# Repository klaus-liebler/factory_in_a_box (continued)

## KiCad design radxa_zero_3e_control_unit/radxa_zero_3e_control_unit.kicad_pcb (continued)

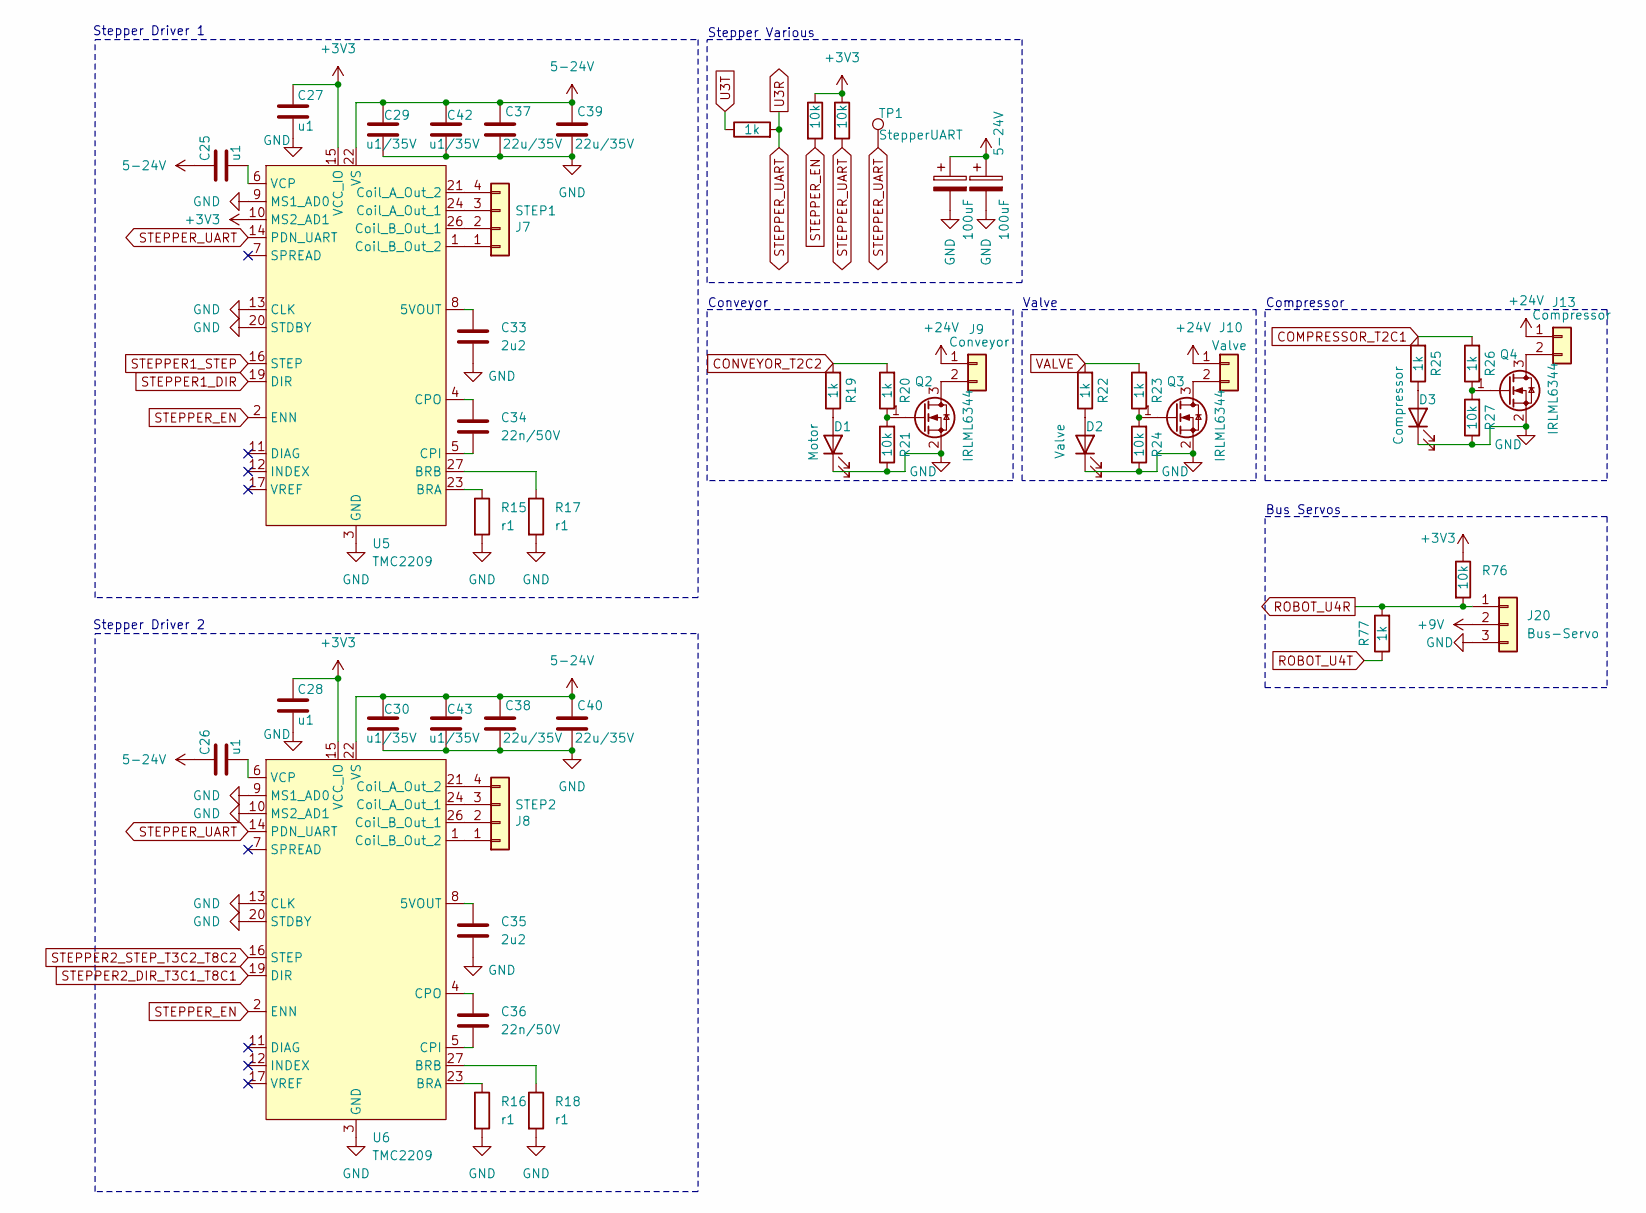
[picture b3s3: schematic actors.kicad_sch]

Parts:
C23, C24: 100uF; CP_Radial_D8.0mm_P2.50mm
C25, C26: u1; C_0805_2012Metric; MPN GRM033R61A104KE15D
C27, C28: u1; C_0402_1005Metric; MPN GRM033R61A104KE15D
C29, C30, C42, C43: u1/35V; C_0805_2012Metric; MPN CC0603KRX7R9BB104
C33, C35: 2u2; C_0402_1005Metric; MPN CL05A225MQ5NSNC
C34, C36: 22n/50V; C_0402_1005Metric; MPN GRM155R71H223KA12D
C37, C38, C39, C40: 22u/35V; C_0805_2012Metric; MPN CGA0805X5R226M350MT
D1: Motor; LED_1206_3216Metric_ReverseMount; MPN LTST-C230KRKT
D2: Valve; LED_1206_3216Metric_ReverseMount; MPN LTST-C230KRKT
D3: Compressor; LED_1206_3216Metric_ReverseMount; MPN LTST-C230KRKT
J7: STEP1; JST_XH_B4B-XH-A_1x04_P2.50mm_Vertical_smaller; MPN XH-4AW
J8: STEP2; JST_XH_B4B-XH-A_1x04_P2.50mm_Vertical_smaller; MPN XH-4AW
J9: Conveyor; PhoenixContact_MC_1,5_2-G-3.5_1x02_P3.50mm_Horizontal_small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
J10: Valve; PhoenixContact_MC_1,5_2-G-3.5_1x02_P3.50mm_Horizontal_small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
J13: Compressor; PhoenixContact_MC_1,5_2-G-3.5_1x02_P3.50mm_Horizontal_small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
J20: Bus-Servo; Molex_SPOX_5267-03A_1x03_P2.50mm_Vertical; MPN 5267-03A / 22035035
Q2, Q3, Q4: IRLML6344; SOT-23; MPN AO3400
R1, R77: 1k; R_0402_1005Metric
R9, R10, R76: 10k; R_0402_1005Metric
R15, R16, R17, R18: r1; R_1206_3216Metric; MPN FRM121WFR100TM
R19, R20, R22, R23, R25, R26: 1k; R_0402_1005Metric; MPN 0402WGF1001TCE
R21, R24, R27: 10k; R_0402_1005Metric; MPN 0201WMF1002TEE
TP1: StepperUART; TestPoint_THTPad_D1.0mm_Drill0.5mm
U5, U6: TMC2209; QFN-28-1EP_5x5mm_P0.5mm_EP3.75x3.75mm_ThermalVias; MPN TMC2209-LA-T

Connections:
5-24V: C23.1, C24.1, C25.1, C26.1, C29.1, C30.1, C37.2, C38.2, C39.2, C40.2, C42.1, C43.1, U5.22 (VS), U5.28 (VS), U6.22 (VS), U6.28 (VS); also elsewhere on the board
+3V3: C27.1, C28.1, R9.1, R10.1, R76.1, U5.10 (MS2_AD1), U5.15 (VCC_IO), U6.15 (VCC_IO); also elsewhere on the board
+9V: J20.2; also elsewhere on the board
+24V: J9.1, J10.1, J13.1; also elsewhere on the board
COMPRESSOR_T2C1: R25.2, R26.2; also elsewhere on the board
CONVEYOR_T2C2: R19.2, R20.2; also elsewhere on the board
GND: C23.2, C24.2, C27.2, C28.2, C29.2, C30.2, C33.2, C35.2, C37.1, C38.1, C39.1, C40.1, C42.2, C43.2, D1.1 (K), D2.1 (K), D3.1 (K), J20.3, Q2.2 (S), Q3.2 (S), Q4.2 (S), R15.2, R16.2, R17.2, R18.2, R21.1, R24.1, R27.1, U5.3 (GND), U5.9 (MS1_AD0), U5.13 (CLK), U5.18 (GND), U5.20 (STDBY), U5.25 (GND), U5.29 (PAD), U6.3 (GND), U6.9 (MS1_AD0), U6.10 (MS2_AD1), U6.13 (CLK), U6.18 (GND), U6.20 (STDBY), U6.25 (GND), U6.29 (PAD); also elsewhere on the board
unnamed: D1.2 (A), R19.1
unnamed: D2.2 (A), R22.1
unnamed: D3.2 (A), R25.1
unnamed: J7.1, U5.1 (Coil_B_Out_2)
unnamed: J7.2, U5.26 (Coil_B_Out_1)
unnamed: J7.3, U5.24 (Coil_A_Out_1)
unnamed: J7.4, U5.21 (Coil_A_Out_2)
unnamed: J8.1, U6.1 (Coil_B_Out_2)
unnamed: J8.2, U6.26 (Coil_B_Out_1)
unnamed: J8.3, U6.24 (Coil_A_Out_1)
unnamed: J8.4, U6.21 (Coil_A_Out_2)
unnamed: J9.2, Q2.3 (D)
unnamed: J10.2, Q3.3 (D)
unnamed: J13.2, Q4.3 (D)
unnamed: Q2.1 (G), R20.1, R21.2
unnamed: Q3.1 (G), R23.1, R24.2
unnamed: Q4.1 (G), R26.1, R27.2
unnamed: C33.1, U5.8 (5VOUT)
unnamed: R15.1, U5.23 (BRA)
unnamed: R17.1, U5.27 (BRB)
unnamed: C34.2, U5.5 (CPI)
unnamed: C34.1, U5.4 (CPO)
unnamed: C25.2, U5.6 (VCP)
unnamed: C35.1, U6.8 (5VOUT)
unnamed: R16.1, U6.23 (BRA)
unnamed: R18.1, U6.27 (BRB)
unnamed: C36.2, U6.5 (CPI)
unnamed: C36.1, U6.4 (CPO)
unnamed: C26.2, U6.6 (VCP)
ROBOT_U4R: J20.1, R76.2, R77.2; also elsewhere on the board
ROBOT_U4T: R77.1; also elsewhere on the board
STEPPER1_DIR: U5.19 (DIR); also elsewhere on the board
STEPPER1_STEP: U5.16 (STEP); also elsewhere on the board
STEPPER2_DIR_T3C1_T8C1: U6.19 (DIR); also elsewhere on the board
STEPPER2_STEP_T3C2_T8C2: U6.16 (STEP); also elsewhere on the board
STEPPER_EN: R9.2, U5.2 (ENN), U6.2 (ENN); also elsewhere on the board
STEPPER_UART: R1.2, R10.2, TP1.1, U5.14 (PDN_UART), U6.14 (PDN_UART); also elsewhere on the board
U3T: R1.1; also elsewhere on the board
VALVE: R22.2, R23.2; also elsewhere on the board

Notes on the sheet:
Stepper Driver 2
Valve
Stepper Various
Bus Servos
Stepper Driver 1
Conveyor
Compressor

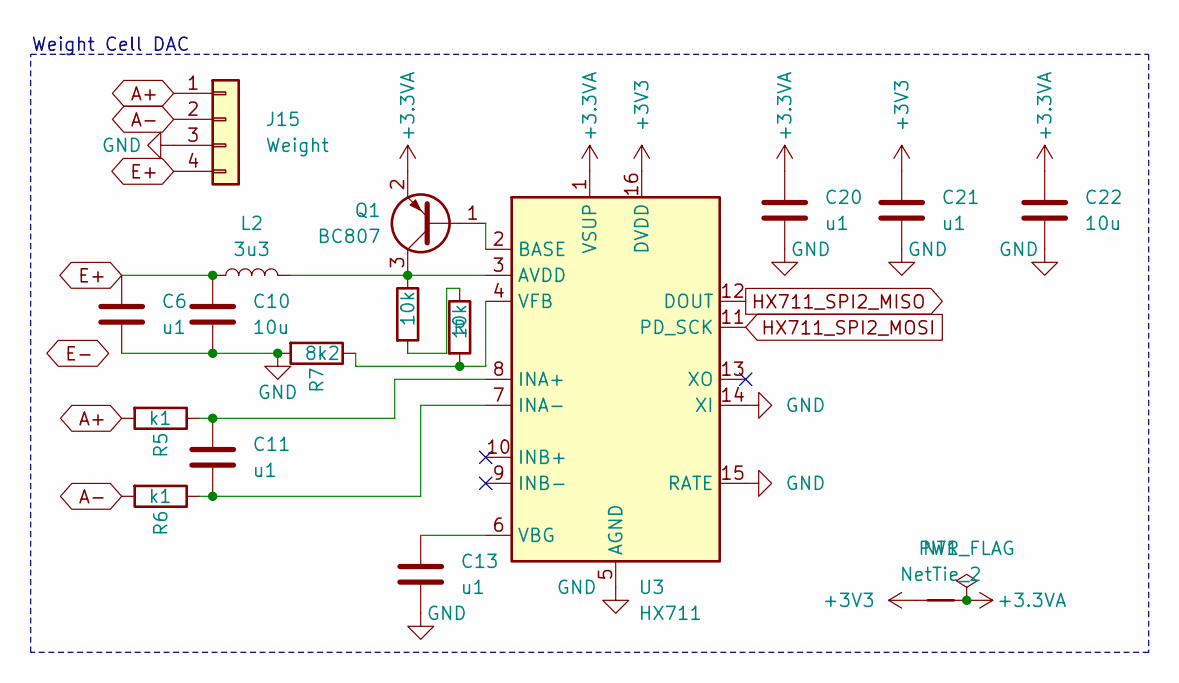
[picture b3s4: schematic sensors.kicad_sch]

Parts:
C6, C11, C13, C20, C21: u1; C_0402_1005Metric
C10, C22: 10u; C_0805_2012Metric_Pad1.18x1.45mm_HandSolder
J15: Weight; JST_XH_B4B-XH-A_1x04_P2.50mm_Vertical_smaller
L2: 3u3; L_0805_2012Metric_Pad1.15x1.40mm_HandSolder
NT1: NetTie_2; NetTie-2_SMD_Pad0.5mm
Q1: BC807; SOT-23_smaller
R5, R6: k1; R_0402_1005Metric
R7: 8k2; R_0402_1005Metric
R8, R11: 10k; R_0402_1005Metric
U3: HX711; SOIC-16_3.9x9.9mm_P1.27mm

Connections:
+3.3VA: C20.1, C22.1, NT1.2, Q1.2 (E), U3.1 (VSUP)
+3V3: C21.1, NT1.1, U3.16 (DVDD); also elsewhere on the board
A+: J15.1, R5.2
A-: J15.2, R6.2
E+: C6.1, C10.1, J15.4, L2.1
GND: C6.2, C10.2, C13.2, C20.2, C21.2, C22.2, J15.3, R7.2, U3.5 (AGND), U3.14 (XI), U3.15 (RATE); also elsewhere on the board
HX711_SPI2_MISO: U3.12 (DOUT); also elsewhere on the board
HX711_SPI2_MOSI: U3.11 (PD_SCK); also elsewhere on the board
unnamed: Q1.1 (B), U3.2 (BASE)
unnamed: L2.2, Q1.3 (C), R8.1, U3.3 (AVDD)
unnamed: R8.2, R11.1
unnamed: C11.1, R5.1, U3.8 (INA+)
unnamed: C11.2, R6.1, U3.7 (INA-)
unnamed: C13.1, U3.6 (VBG)
unnamed: R7.1, R11.2, U3.4 (VFB)

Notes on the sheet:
Weight Cell DAC

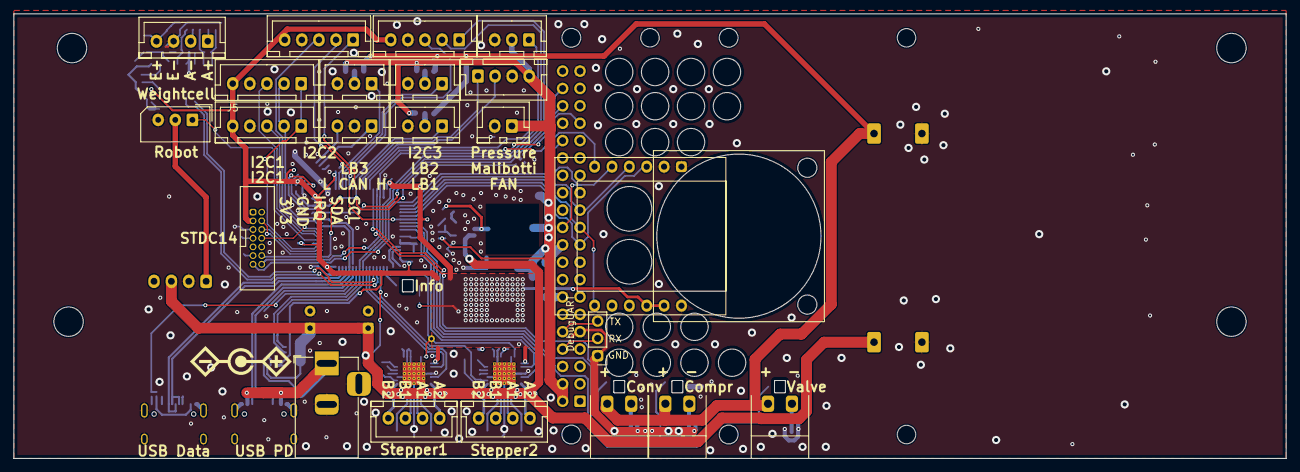
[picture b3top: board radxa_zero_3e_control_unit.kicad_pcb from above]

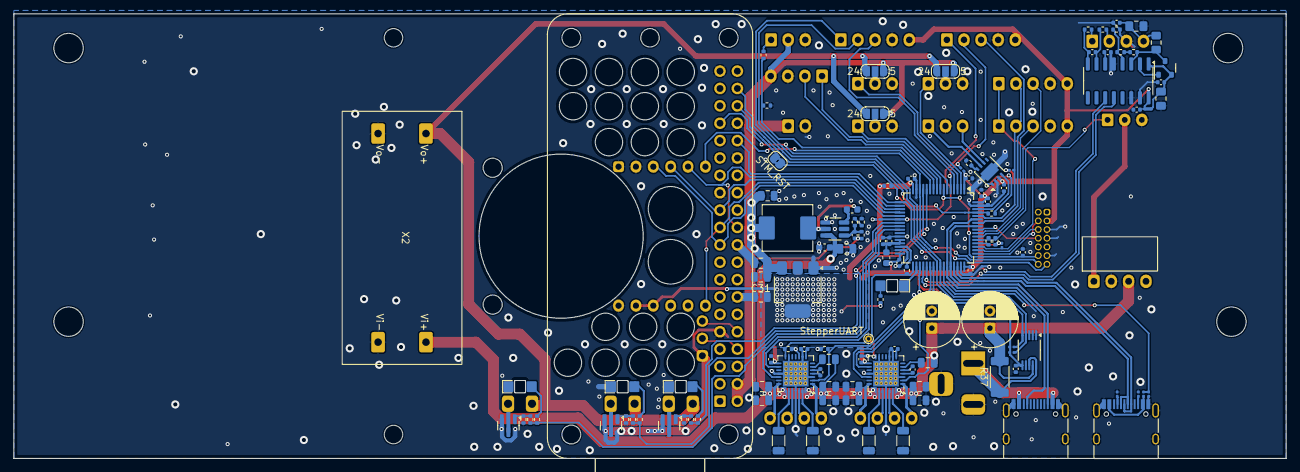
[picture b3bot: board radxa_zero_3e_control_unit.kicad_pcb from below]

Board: 2 copper layers, 186.0 x 65.0 mm, 148 parts (117 on the bottom side), 116 nets.

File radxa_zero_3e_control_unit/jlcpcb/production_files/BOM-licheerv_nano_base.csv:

Comment,Designator,Footprint,LCSC,Quantity
56p,C4,C_0402_1005Metric,C107007,1
1k,"R1,R19,R20,R22,R23,R25,R26",R_0402_1005Metric,C11702,7
Motor,"D1,D2,D3",LED_1206_3216Metric_ReverseMount,C125107,3
u1/35V,"C1,C3",C_0603_1608Metric,C14663,2
3u3,L2,L_0805_2012Metric_Pad1.15x1.40mm_HandSolder,C162585,1
USB STM32,"J1,J22",USB_C_Receptacle_HRO_TYPE-C-31-M-12_smaller,C165948,2
2u2,"C33,C35,C8",C_0402_1005Metric,C170151,3
TPS54202DDC,U1,SOT-23-6_Handsoldering,C191884,1
600R,FB1,L_0603_1608Metric,C19330,1
TMC2209,"U5,U6",QFN-28-1EP_5x5mm_P0.5mm_EP3.75x3.75mm_ThermalVias,C2150710,2
4u7,C14,C_0402_1005Metric,C23733,1
k1,"R5,R6",R_0402_1005Metric,C25076,2
r1,"R15,R16,R17,R18",R_1206_3216Metric,C25334,4
3k3,R4,R_0402_1005Metric,C25890,1
8k2,R7,R_0402_1005Metric,C25924,1
5k1,"R13,R28",R_0201_0603Metric,C270344,2
22n/50V,"C34,C36",C_0402_1005Metric,C337699,2
IRLML6344,"Q2,Q3,Q4",SOT-23,C347475,3
10uH,L1,L_Abracon_ASPI-0630LR,C408449,1
STM32G431RBTx,U2,LQFP-64_10x10mm_P0.5mm,C431633,1
10k,"R10,R11,R21,R24,R27,R3,R8,R9",R_0201_0603Metric,C473048,8
u1,"C25,C26,C29,C30,C42,C43",C_0805_2012Metric,C49678,6
BC807,Q1,SOT-23_smaller,C57316,1
M1,R2,R_0402_1005Metric,C60491,1
10u,"C10,C2,C22",C_0805_2012Metric_Pad1.18x1.45mm_HandSolder,C6119888,3
22u/35V,"C37,C38,C39,C40,C5,C7",C_0805_2012Metric,C6119901,6
HX711,U3,SOIC-16_3.9x9.9mm_P1.27mm,C6705483,1
u1,"C11,C12,C13,C15,C16,C17,C18,C19,C20,C21,C27,C28,C6,C9",C_0201_0603Metric,C76934,14

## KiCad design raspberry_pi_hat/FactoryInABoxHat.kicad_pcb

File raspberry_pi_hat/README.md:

This is a Raspberry PI Hat for controlling the "Factory-In-A-Box"-Station. KiCad-9.0-Project

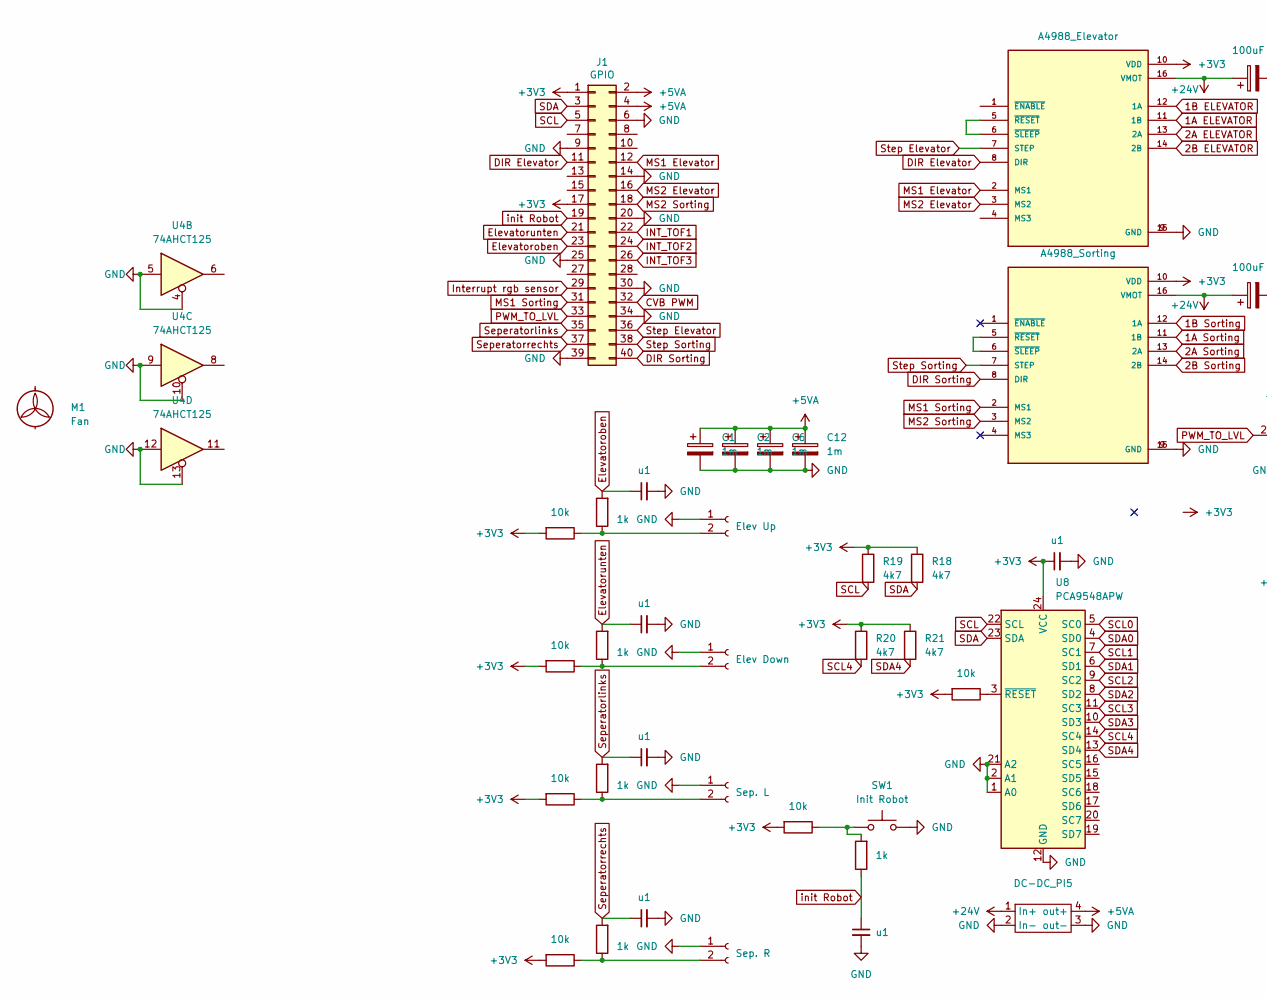
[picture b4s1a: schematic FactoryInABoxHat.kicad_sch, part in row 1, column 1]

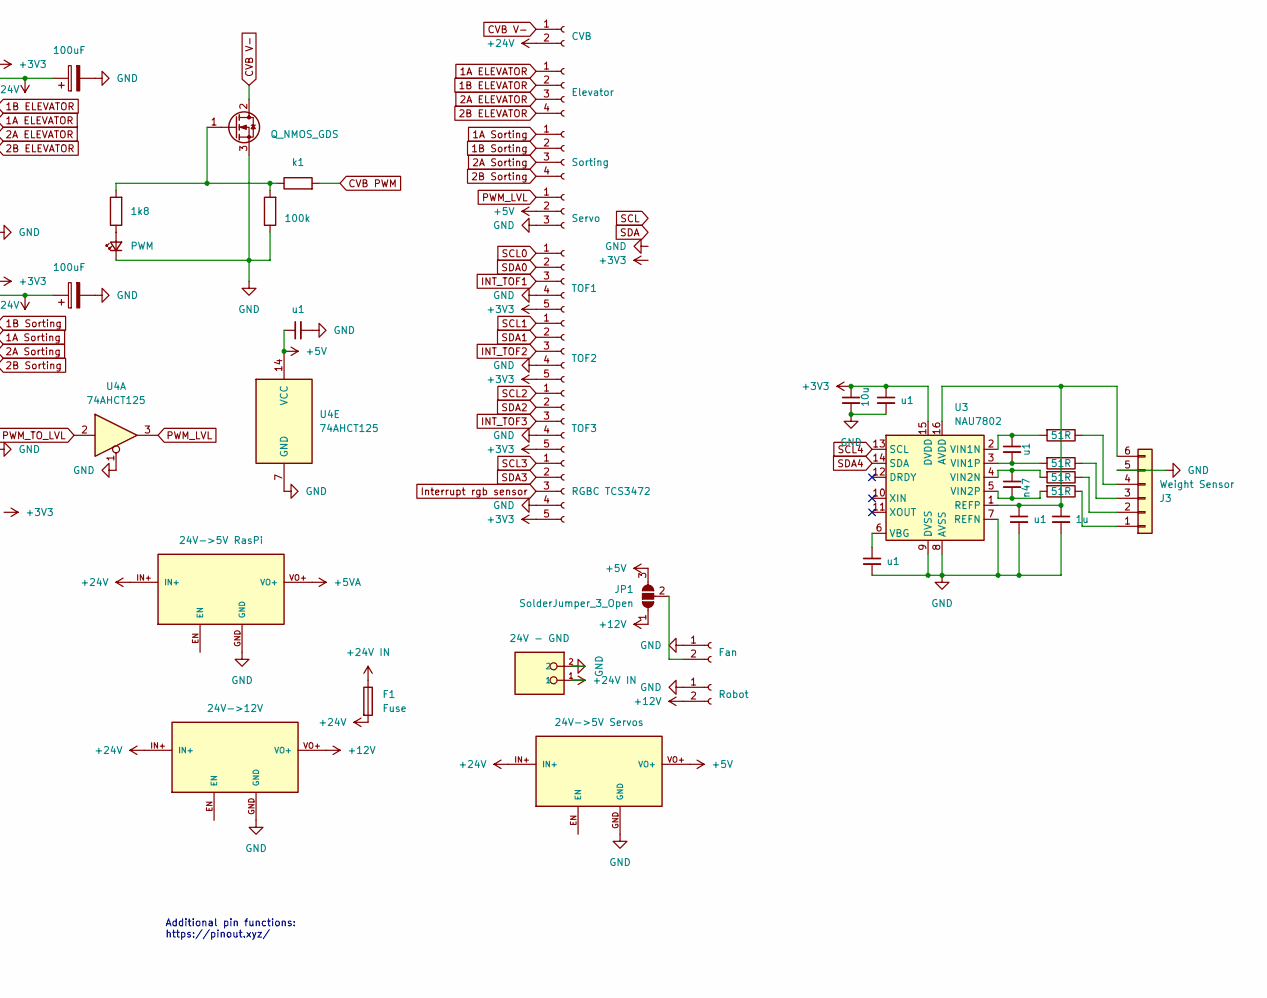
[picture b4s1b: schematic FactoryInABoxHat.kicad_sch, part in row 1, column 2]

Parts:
C1, C2, C6, C12: 1m; CP_Radial_D8.0mm_P5.00mm
C3, C7, C8, C9, C10, C11, C13, C14, C16, C18, C20: u1; C_0805_2012Metric_Pad1.18x1.45mm_HandSolder
C4, C5: 100uF; CP_Radial_D6.3mm_P2.50mm
C15: 1u; C_0805_2012Metric_Pad1.18x1.45mm_HandSolder
C17: 10u; C_0805_2012Metric_Pad1.18x1.45mm_HandSolder
C19: n47; C_0805_2012Metric_Pad1.18x1.45mm_HandSolder
D1: PWM; LED_0805_2012Metric_Pad1.15x1.40mm_HandSolder
DC-DC_PI5: DCDC-XL4015
F1: Fuse; Fuseholder_Cylinder-5x20mm_Schurter_0031_8201_Horizontal_Op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
J1: GPIO; PinSocket_2x20_P2.54mm_Vertical
J2: Servo; JST_XH_B3B-XH-A_1x03_P2.50mm_Vertical
J3: Weight Sensor; JST_XH_B6B-XH-A_1x06_P2.50mm_Vertical
J7: CVB; JST_XH_B2B-XH-A_1x02_P2.50mm_Vertical
J8: Elevator; JST_XH_B4B-XH-A_1x04_P2.50mm_Vertical
J9: RGBC TCS3472; JST_XH_B5B-XH-A_1x05_P2.50mm_Vertical
J10: Robot; JST_XH_B2B-XH-A_1x02_P2.50mm_Vertical
J11: Fan; JST_XH_B2B-XH-A_1x02_P2.50mm_Vertical
J12: Sep. L; JST_XH_B2B-XH-A_1x02_P2.50mm_Vertical
J13: Sorting; JST_XH_B4B-XH-A_1x04_P2.50mm_Vertical
J15: 24V - GND; TerminalBlock_Phoenix_MKDS-1,5-2-5.08_1x02_P5.08mm_Horizont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; PARTREV 28.07.2023
J17: TOF3; JST_XH_B5B-XH-A_1x05_P2.50mm_Vertical
J18: TOF2; JST_XH_B5B-XH-A_1x05_P2.50mm_Vertical
J19: TOF1; JST_XH_B5B-XH-A_1x05_P2.50mm_Vertical
J20: Elev Up; JST_XH_B2B-XH-A_1x02_P2.50mm_Vertical
J21: Elev Down; JST_XH_B2B-XH-A_1x02_P2.50mm_Vertical
J22: Sep. R; JST_XH_B2B-XH-A_1x02_P2.50mm_Vertical
JP1: SolderJumper_3_Open; SolderJumper-3_P1.3mm_Open_RoundedPad1.0x1.5mm
M1: Fan; FAN2507
Q3: Q_NMOS_GDS; TO-220-3_Vertical
R1: k1; R_0805_2012Metric_Pad1.20x1.40mm_HandSolder
R2: 1k8; R_0805_2012Metric_Pad1.20x1.40mm_HandSolder
R3: 100k; R_0805_2012Metric_Pad1.20x1.40mm_HandSolder
R4, R5, R6, R17: 51R; R_0805_2012Metric_Pad1.20x1.40mm_HandSolder
R7, R9, R11, R13, R16, R22: 10k; R_0805_2012Metric_Pad1.20x1.40mm_HandSolder
R8, R10, R12, R14, R15: 1k; R_0805_2012Metric_Pad1.20x1.40mm_HandSolder
R18, R19, R20, R21: 4k7; R_0805_2012Metric_Pad1.20x1.40mm_HandSolder
SW1: Init Robot; SW_PUSH_6mm
U1: A4988_Elevator; MODULE_A4988_STEPPER_MOTOR_DRIVER_CARRIER
U2: A4988_Sorting; MODULE_A4988_STEPPER_MOTOR_DRIVER_CARRIER
U3: NAU7802; SOP-16_3.9x9.9mm_P1.27mm
U4: 74AHCT125
U5: 24V->5V Servos; DCDC_HW613
U6: 24V->12V; DCDC_HW613
U7: 24V->5V RasPi; DCDC_HW613
U8: PCA9548APW; TSSOP-24_4.4x7.8mm_P0.65mm

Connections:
1A ELEVATOR: J8.1, U1.11 (1B)
1A Sorting: J13.1, U2.11 (1B)
1B ELEVATOR: J8.2, U1.12 (1A)
1B Sorting: J13.2, U2.12 (1A)
2A ELEVATOR: J8.3, U1.13 (2A)
2A Sorting: J13.3, U2.13 (2A)
2B ELEVATOR: J8.4, U1.14 (2B)
2B Sorting: J13.4, U2.14 (2B)
+3V3: C11.1, C16.1, C17.1, J1.1, J1.17, J9.5, J17.5, J18.5, J19.5, R7.2, R9.2, R11.2, R13.2, R16.2, R18.1, R19.1, R20.1, R21.1, R22.2, U1.10 (VDD), U2.10 (VDD), U3.15 (DVDD), U8.24 (VCC)
+5V: C20.1, J2.2, JP1.3 (B), U4.14 (VCC), U5.VO+
+5VA: C1.1, C2.1, C6.1, C12.1, DC-DC_PI5.4 (out+), J1.2, J1.4, U7.VO+
+12V: J10.2, JP1.1 (A), U6.VO+
+24V: C4.1, C5.1, DC-DC_PI5.1 (In+), F1.2, J7.2, U1.16 (VMOT), U2.16 (VMOT), U5.IN+, U6.IN+, U7.IN+
+24V IN: F1.1, J15.1
CVB PWM: J1.32, R1.2
CVB V-: J7.1, Q3.2 (D)
DIR Elevator: J1.11, U1.8 (DIR)
DIR Sorting: J1.40, U2.8 (DIR)
Elevatoroben: C7.1, J1.23, R10.2
Elevatorunten: C8.1, J1.21, R12.2
GND: C1.2, C2.2, C3.2, C4.2, C5.2, C6.2, C7.2, C8.2, C9.2, C10.2, C11.2, C12.2, C13.2, C14.2, C15.2, C16.2, C17.2, C20.2, D1.1 (K), DC-DC_PI5.2 (In-), DC-DC_PI5.3 (out-), J1.6, J1.9, J1.14, J1.20, J1.25, J1.30, J1.34, J1.39, J2.3, J3.5, J9.4, J10.1, J11.1, J12.1, J15.2, J17.4, J18.4, J19.4, J20.1, J21.1, J22.1, Q3.3 (S), R3.1, SW1.2, U1.9 (GND), U1.15 (GND), U2.9 (GND), U2.15 (GND), U3.7 (REFN), U3.8 (AVSS), U3.9 (DVSS), U4.1, U4.4, U4.5, U4.7 (GND), U4.9, U4.10, U4.12, U4.13, U5.GND, U6.GND, U7.GND, U8.1 (A0), U8.2 (A1), U8.12 (GND), U8.21 (A2)
INT_TOF1: J1.22, J19.3
INT_TOF2: J1.24, J18.3
INT_TOF3: J1.26, J17.3
Interrupt rgb sensor: J1.29, J9.3
MS1 Elevator: J1.12, U1.2 (MS1)
MS1 Sorting: J1.31, U2.2 (MS1)
MS2 Elevator: J1.16, U1.3 (MS2)
MS2 Sorting: J1.18, U2.3 (MS2)
unnamed: D1.2 (A), R2.1
unnamed: J3.1, R17.1
unnamed: J3.2, R6.1
unnamed: J3.3, R5.1
unnamed: J3.4, R4.1
unnamed: C14.1, C15.1, J3.6, U3.1 (REFP), U3.16 (AVDD)
unnamed: J11.2, JP1.2 (C)
unnamed: J12.2, R7.1, R8.1
unnamed: J20.2, R9.1, R10.1
unnamed: J21.2, R11.1, R12.1
unnamed: J22.2, R13.1, R14.1
unnamed: Q3.1 (G), R1.1, R2.2, R3.2
unnamed: R15.2, R16.1, SW1.1
unnamed: U1.5 (~RESET), U1.6 (~SLEEP)
unnamed: U2.5 (~RESET), U2.6 (~SLEEP)
unnamed: C13.1, U3.6 (VBG)
unnamed: C18.1, R4.2, U3.2 (VIN1N)
unnamed: C18.2, R5.2, U3.3 (VIN1P)
unnamed: C19.1, R6.2, U3.4 (VIN2N)
unnamed: C19.2, R17.2, U3.5 (VIN2P)
unnamed: R22.1, U8.3 (~RESET)
PWM_LVL: J2.1, U4.3
PWM_TO_LVL: J1.33, U4.2
SCL: J1.5, R19.2, U8.22 (SCL)
SCL0: J19.1, U8.5 (SC0)
SCL1: J18.1, U8.7 (SC1)
SCL2: J17.1, U8.9 (SC2)
SCL3: J9.1, U8.11 (SC3)
SCL4: R20.2, U3.13 (SCL), U8.14 (SC4)
SDA: J1.3, R18.2, U8.23 (SDA)
SDA0: J19.2, U8.4 (SD0)
SDA1: J18.2, U8.6 (SD1)
SDA2: J17.2, U8.8 (SD2)
SDA3: J9.2, U8.10 (SD3)
SDA4: R21.2, U3.14 (SDA), U8.13 (SD4)
Seperatorlinks: C3.1, J1.35, R8.2
Seperatorrechts: C9.1, J1.37, R14.2
Step Elevator: J1.36, U1.7 (STEP)
Step Sorting: J1.38, U2.7 (STEP)
init Robot: C10.1, J1.19, R15.1

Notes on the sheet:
Additional pin functions: https://pinout.xyz/

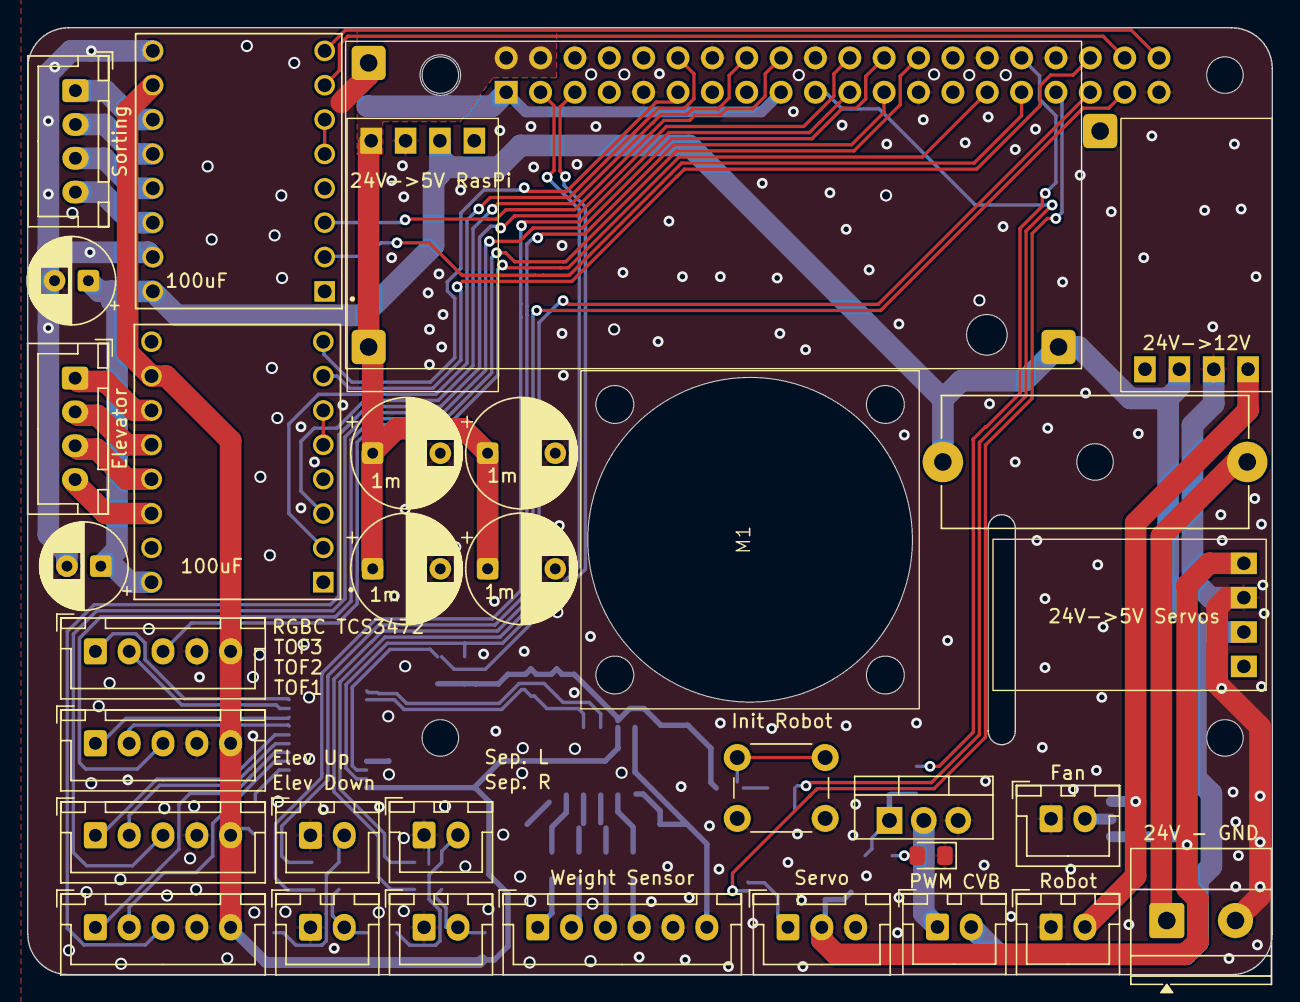
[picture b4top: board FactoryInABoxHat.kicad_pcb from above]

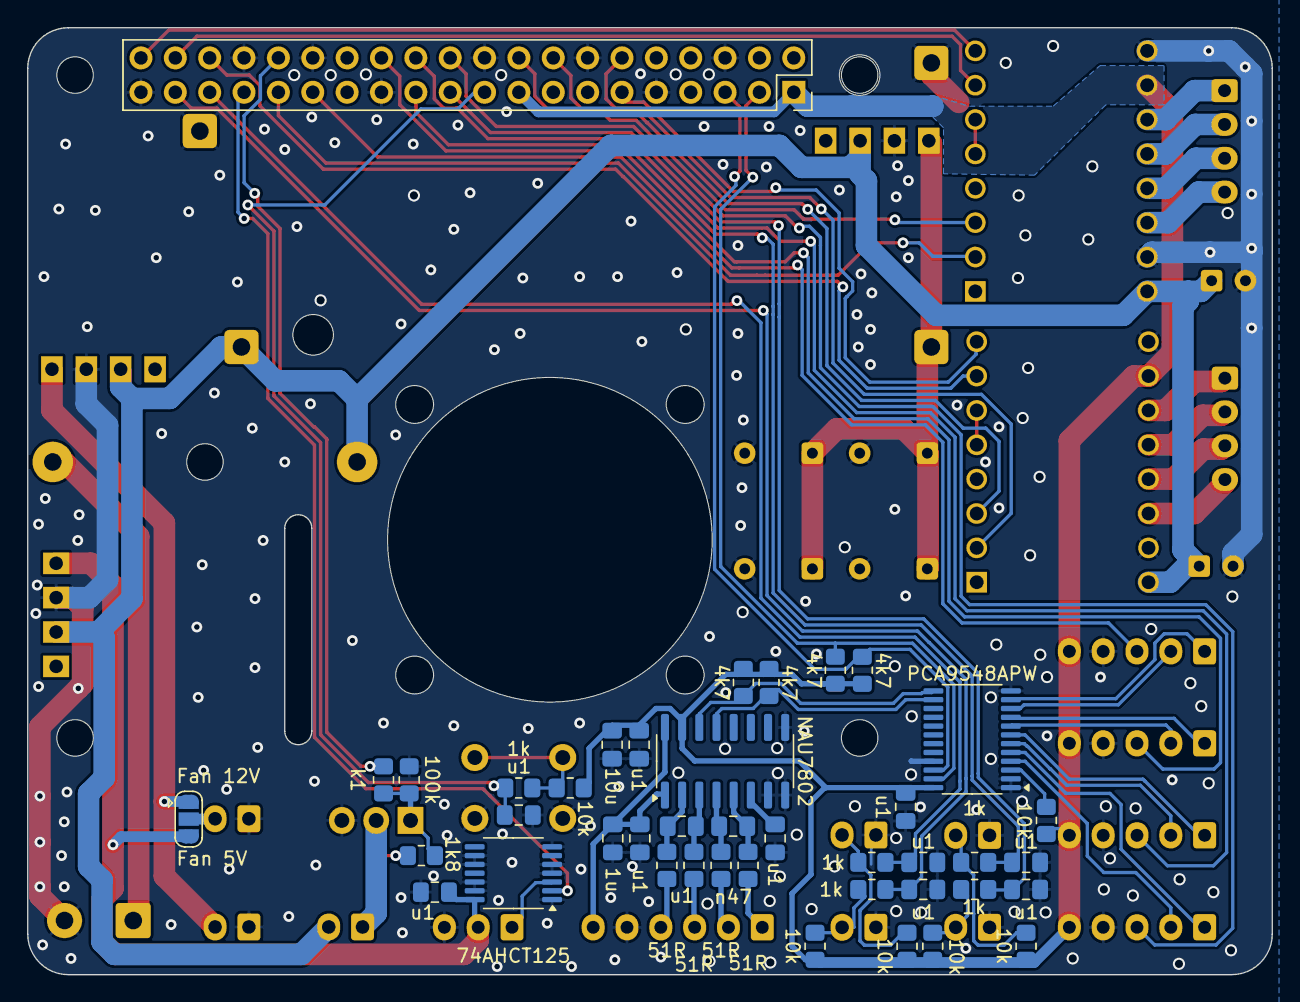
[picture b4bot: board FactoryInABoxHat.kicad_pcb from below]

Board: 2 copper layers, 92.0 x 70.0 mm, 78 parts (41 on the bottom side), 69 nets.

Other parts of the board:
MH1, MH2, MH3, MH4: MountingHole_2.7mm_M2.5

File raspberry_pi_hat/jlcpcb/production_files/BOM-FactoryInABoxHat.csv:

Comment,Designator,Footprint,LCSC,Quantity
100uF,C4,CP_Radial_D6.3mm_P2.50mm,C2035,1
RGBC TCS3472,J9,JST_XH_B5B-XH-A_1x05_P2.50mm_Vertical,,1
24V->5V Servos,U5,DCDC_HW613,,1
Weight Sensor,J3,JST_XH_B6B-XH-A_1x06_P2.50mm_Vertical,,1
TOF1,J19,JST_XH_B5B-XH-A_1x05_P2.50mm_Vertical,,1
CVB,J7,JST_XH_B2B-XH-A_1x02_P2.50mm_Vertical,,1
Fan,J11,JST_XH_B2B-XH-A_1x02_P2.50mm_Vertical,,1
A4988_Sorting,U2,MODULE_A4988_STEPPER_MOTOR_DRIVER_CARRIER,,1
1m,C12,CP_Radial_D8.0mm_P5.00mm,,1
Servo,J2,JST_XH_B3B-XH-A_1x03_P2.50mm_Vertical,,1
100uF,C5,CP_Radial_D6.3mm_P2.50mm,,1
24V - GND,J15,"TerminalBlock_Phoenix_MKDS-1,5-2-5.08_1x02_P5.08mm_Horizontal",,1
Elev Up,J20,JST_XH_B2B-XH-A_1x02_P2.50mm_Vertical,,1
1m,C1,CP_Radial_D8.0mm_P5.00mm,,1
Q_NMOS_GDS,Q3,TO-220-3_Vertical,,1
24V->12V,U6,DCDC_HW613,,1
1m,C6,CP_Radial_D8.0mm_P5.00mm,,1
Robot,J10,JST_XH_B2B-XH-A_1x02_P2.50mm_Vertical,,1
Fan,M1,FAN2507,,1
Sep. L,J12,JST_XH_B2B-XH-A_1x02_P2.50mm_Vertical,,1
Elevator,J8,JST_XH_B4B-XH-A_1x04_P2.50mm_Vertical,,1
TOF2,J18,JST_XH_B5B-XH-A_1x05_P2.50mm_Vertical,,1
24V->5V RasPi,U7,DCDC_HW613,,1
Sep. R,J22,JST_XH_B2B-XH-A_1x02_P2.50mm_Vertical,,1
Sorting,J13,JST_XH_B4B-XH-A_1x04_P2.50mm_Vertical,,1
PWM,D1,LED_0805_2012Metric_Pad1.15x1.40mm_HandSolder,,1
Init Robot,SW1,SW_PUSH_6mm,,1
Fuse,F1,Fuseholder_Cylinder-5x20mm_Schurter_0031_8201_Horizontal_Open,,1
TOF3,J17,JST_XH_B5B-XH-A_1x05_P2.50mm_Vertical,,1
1m,C2,CP_Radial_D8.0mm_P5.00mm,,1
A4988_Elevator,U1,MODULE_A4988_STEPPER_MOTOR_DRIVER_CARRIER,,1
Elev Down,J21,JST_XH_B2B-XH-A_1x02_P2.50mm_Vertical,,1
GPIO,J1,PinSocket_2x20_P2.54mm_Vertical,,1
1k8,R2,R_0805_2012Metric_Pad1.20x1.40mm_HandSolder,,1
u1,C16,C_0805_2012Metric_Pad1.18x1.45mm_HandSolder,,1
10u,C17,C_0805_2012Metric_Pad1.18x1.45mm_HandSolder,,1
100k,R3,R_0805_2012Metric_Pad1.20x1.40mm_HandSolder,,1
10k,R9,R_0805_2012Metric_Pad1.20x1.40mm_HandSolder,,1
NAU7802,U3,SOP-16_3.9x9.9mm_P1.27mm,,1
1k,R10,R_0805_2012Metric_Pad1.20x1.40mm_HandSolder,,1
51R,R4,R_0805_2012Metric_Pad1.20x1.40mm_HandSolder,,1
u1,C10,C_0805_2012Metric_Pad1.18x1.45mm_HandSolder,,1
10k,R16,R_0805_2012Metric_Pad1.20x1.40mm_HandSolder,,1
u1,C20,C_0805_2012Metric_Pad1.18x1.45mm_HandSolder,,1
u1,C18,C_0805_2012Metric_Pad1.18x1.45mm_HandSolder,,1
1k,R15,R_0805_2012Metric_Pad1.20x1.40mm_HandSolder,,1
1k,R8,R_0805_2012Metric_Pad1.20x1.40mm_HandSolder,,1
u1,C11,C_0805_2012Metric_Pad1.18x1.45mm_HandSolder,,1
u1,C8,C_0805_2012Metric_Pad1.18x1.45mm_HandSolder,,1
1k,R14,R_0805_2012Metric_Pad1.20x1.40mm_HandSolder,,1
51R,R17,R_0805_2012Metric_Pad1.20x1.40mm_HandSolder,,1
4k7,R20,R_0805_2012Metric_Pad1.20x1.40mm_HandSolder,,1
10k,R11,R_0805_2012Metric_Pad1.20x1.40mm_HandSolder,,1
n47,C19,C_0805_2012Metric_Pad1.18x1.45mm_HandSolder,,1
4k7,R18,R_0805_2012Metric_Pad1.20x1.40mm_HandSolder,,1
4k7,R19,R_0805_2012Metric_Pad1.20x1.40mm_HandSolder,,1
4k7,R21,R_0805_2012Metric_Pad1.20x1.40mm_HandSolder,,1
1k,R12,R_0805_2012Metric_Pad1.20x1.40mm_HandSolder,,1
74AHCT125,U4,TSSOP-14_4.4x5mm_P0.65mm,,1
1u,C15,C_0805_2012Metric_Pad1.18x1.45mm_HandSolder,,1
u1,C9,C_0805_2012Metric_Pad1.18x1.45mm_HandSolder,,1
u1,C14,C_0805_2012Metric_Pad1.18x1.45mm_HandSolder,,1
51R,R6,R_0805_2012Metric_Pad1.20x1.40mm_HandSolder,,1
10k,R7,R_0805_2012Metric_Pad1.20x1.40mm_HandSolder,,1
u1,C3,C_0805_2012Metric_Pad1.18x1.45mm_HandSolder,,1
PCA9548APW,U8,TSSOP-24_4.4x7.8mm_P0.65mm,,1
u1,C7,C_0805_2012Metric_Pad1.18x1.45mm_HandSolder,,1
u1,C13,C_0805_2012Metric_Pad1.18x1.45mm_HandSolder,,1
k1,R1,R_0805_2012Metric_Pad1.20x1.40mm_HandSolder,,1
51R,R5,R_0805_2012Metric_Pad1.20x1.40mm_HandSolder,,1
10k,R13,R_0805_2012Metric_Pad1.20x1.40mm_HandSolder,,1

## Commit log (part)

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2025-12-14 Initial
2025-12-16 Initial commit lichee_rv_nano_base pcb
2025-12-23 lichee_rv_nano aka radxa zero 3e as ordered @ jlcpcb
2026-01-21 Various
2026-01-21 Iniital version of firmware
2026-01-22 Added usb-pd files
2026-01-25 Fixes
    - air ventilation holes
    - HX711 is on SPI MISO and SPI MOSI according to https://github.com/ufnalski/hx711_non_blocking_spi_g431kb (PC10-->PC11, PC11-->PC12)
    - DC connector polarity changed
    - connectors for voltages
    - TMC2209 got different communication IDs
    - Elkos mor space
2026-01-25 WIP with firmware
2026-01-26 autotune works
2026-01-28 Test Sigmoid
2026-02-08 WIP, before repinning SUM32G431
2026-02-10 Udated control unit pcb
2026-02-14 USB PD Working; requests SourceCapabilities always
2026-02-17 Sigmoid Stepper
2026-02-19 Sigmoid Test Plots
2026-02-26 First time zero errors, but bad layout
2026-03-01 WIP 2nd
2026-03-02 EtherCAT + HX711
2026-03-02 Added HX711
2026-03-07 Various updates
2026-04-01 TMC2209 first run
2026-05-06 New version
2026-05-14 Almost orderable, but: Size is too large to fit
2026-05-15 Release Candidate
2026-05-16 pcb_control_unit_ethercat as ordered @ JLCPCB
